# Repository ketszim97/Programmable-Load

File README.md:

# Programmable-Load
A DIY Open Source Programmable Load

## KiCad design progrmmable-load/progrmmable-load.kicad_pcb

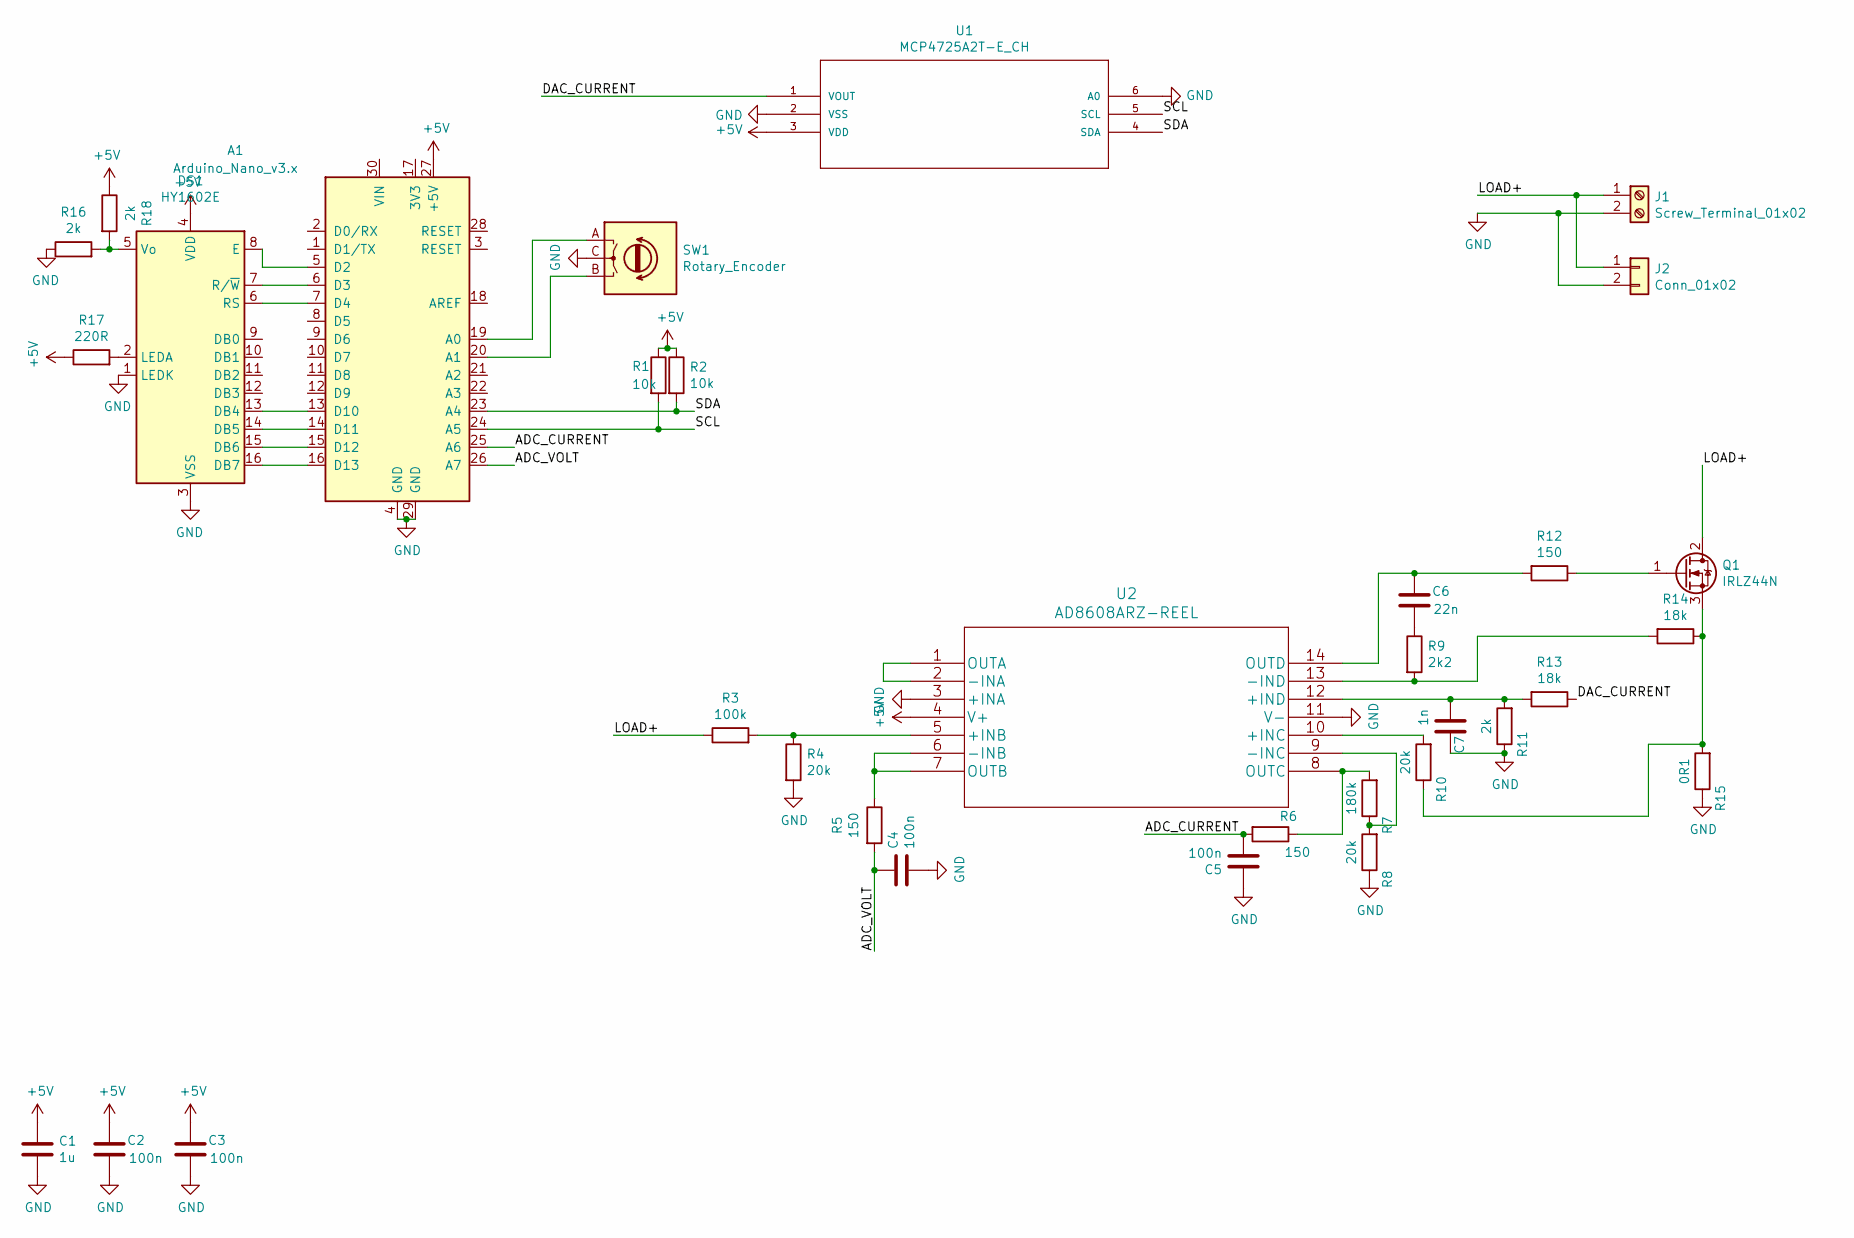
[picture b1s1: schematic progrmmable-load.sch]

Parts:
A1: Arduino_Nano_v3.x; Arduino_Nano
C1: 1u; C_0603_1608Metric
C2, C3, C4, C5: 100n; C_0603_1608Metric
C6: 22n; C_0603_1608Metric
C7: 1n; C_0603_1608Metric
DS1: HY1602E
J1: Screw_Terminal_01x02; TerminalBlock_TE_282834-2_1x02_P2.54mm_Horizontal
J2: Conn_01x02; Banana_Jack_2Pin
Q1: IRLZ44N; TO-220-3_Vertical
R1, R2: 10k; R_0603_1608Metric
R3: 100k; R_0603_1608Metric
R4, R8, R10: 20k; R_0603_1608Metric
R5, R6, R12: 150; R_0603_1608Metric
R7: 180k; R_0603_1608Metric
R9: 2k2; R_0603_1608Metric
R11, R16, R18: 2k; R_0603_1608Metric
R13, R14: 18k; R_0603_1608Metric
R15: 0R1; R_Axial_DIN0309_L9.0mm_D3.2mm_P20.32mm_Horizontal
R17: 220R; R_0603_1608Metric
SW1: Rotary_Encoder; RotaryEncoder_Alps_EC11E-Switch_Vertical_H20mm
U1: MCP4725A2T-E_CH; SOT-23-6_MC
U2: AD8608ARZ-REEL

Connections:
+5V: A1.27 (+5V), C1.2, C2.2, C3.2, DS1.4 (VDD), R1.1, R2.1, R17.1, R18.1, U1.3 (VDD), U2.4 (V+)
/ADC_CURRENT: A1.25 (A6), C5.2, R6.2
/ADC_VOLT: A1.26 (A7), C4.1, R5.2
/DAC_CURRENT: R13.1, U1.1 (VOUT)
/LOAD+: J1.1, J2.1, Q1.2 (D), R3.1
/SCL: A1.24 (A5), R1.2, U1.5 (SCL)
/SDA: A1.23 (A4), R2.2, U1.4 (SDA)
GND: A1.4 (GND), A1.29 (GND), C1.1, C2.1, C3.1, C4.2, C5.1, C7.1, DS1.1 (LEDK), DS1.3 (VSS), J1.2, J2.2, R4.2, R8.1, R11.1, R15.1, R16.1, SW1.C, U1.2 (VSS), U1.6 (A0), U2.3 (+INA), U2.11 (V-)
unnamed: A1.5 (D2), DS1.8 (E)
unnamed: A1.6 (D3), DS1.7 (R/~W)
unnamed: A1.7 (D4), DS1.6 (RS)
unnamed: A1.13 (D10), DS1.13 (DB4)
unnamed: A1.14 (D11), DS1.14 (DB5)
unnamed: A1.15 (D12), DS1.15 (DB6)
unnamed: A1.16 (D13), DS1.16 (DB7)
unnamed: A1.19 (A0), SW1.A
unnamed: A1.20 (A1), SW1.B
unnamed: C6.1, R9.1
unnamed: C6.2, R12.2, U2.14 (OUTD)
unnamed: C7.2, R11.2, R13.2, U2.12 (+IND)
unnamed: DS1.2 (LEDA), R17.2
unnamed: DS1.5 (Vo), R16.2, R18.2
unnamed: Q1.1 (G), R12.1
unnamed: Q1.3 (S), R10.1, R14.1, R15.2
unnamed: R3.2, R4.1, U2.5 (+INB)
unnamed: R5.1, U2.6 (-INB), U2.7 (OUTB)
unnamed: R6.1, R7.2, U2.8 (OUTC)
unnamed: R7.1, R8.2, U2.9 (-INC)
unnamed: R10.2, U2.10 (+INC)
unnamed: R9.2, R14.2, U2.13 (-IND)
unnamed: U2.1 (OUTA), U2.2 (-INA)

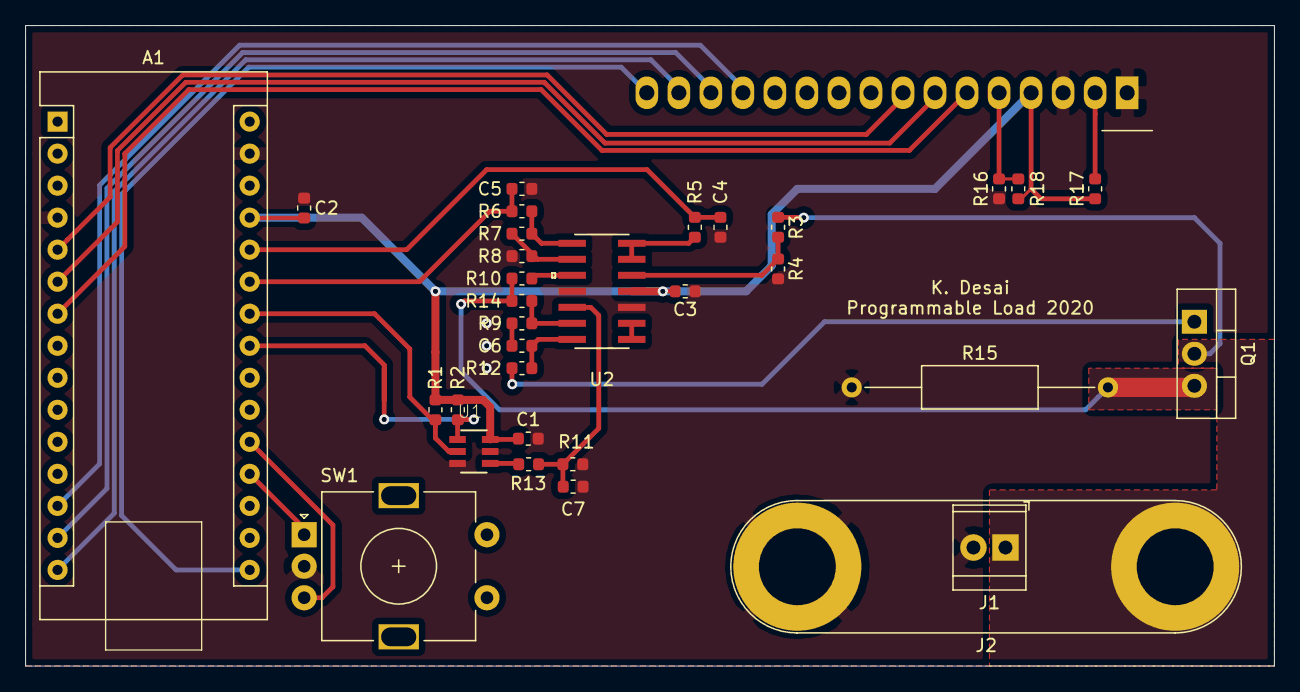
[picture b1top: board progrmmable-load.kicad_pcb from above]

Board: 2 copper layers, 99.1 x 50.8 mm, 33 parts (0 on the bottom side), 31 nets.

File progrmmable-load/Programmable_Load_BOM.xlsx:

Designator | Package | Value | Supplier | Supplier PN | Qty Per Board
U1 | SOT-23-6 | MCP4725A2T | Mouser | 579-MCP4725A2T-E/CH | 1
U2 | 14-SOIC | AD8608ARZ | Mouser | 584-AD8608ARZ-R7 | 1
C1 | 0603 | 1u | Mouser | 963-TMK107B7105MA-T | 1
C2, C3, C4, C5 | 0603 | 100n | Mouser | 80-C0603X104K5R3316 | 4
C6 | 0603 | 22n | Mouser | 581-06036C223KAT2A | 1
C7 | 0603 | 1n | Mouser | 80-C0603C102J5RAUTO | 1
Q1 | TO-220 | IRLZ44N | Mouser | 942-IRLZ44NPBF | 1
R1, R2 | 0603 | 10k | Mouser | 667-ERJ-3EKF1002V | 2
R3 | 0603 | 100k | Mouser | 71-CRCW0603100KFKEAC | 1
R4, R8, R10 | 0603 | 20k | Mouser | 603-RC0603FR-1020KL | 3
R5, R6, R12 | 0603 | 150R | Mouser | 603-RC0603FR-07150RL | 3
R7 | 0603 | 180k | Mouser | 603-RC0603FR-10180KL | 1
R9, R11, R16 | 0603 | 2k2 | Mouser | 71-CRCW06032K20FKEAC | 3
R13, R14 | 0603 | 18k | Mouser | 603-AC0603FR-1318KL | 2
R15 | THT | 0R1 | Mouser | 588-WHDR10FET | 1
R17 | 0603 | 220R | Mouser | 603-RC0603FR-13220RL | 1

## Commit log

2020-03-15 Added programmable load design done in Kicad
2020-04-06 Added BOM file with Mouser PNs
2020-04-12 Generated STEP file to allow for case design
2020-07-18 Add R18 to fix LCD contrast

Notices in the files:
parts and their libraries:
Copyright 2016 Accelerated Designs. All rights reserved.
